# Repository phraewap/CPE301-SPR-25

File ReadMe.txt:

Name: Phraewa Pookprajob

UNLV Email: pookpraj@unlv.nevada.edu

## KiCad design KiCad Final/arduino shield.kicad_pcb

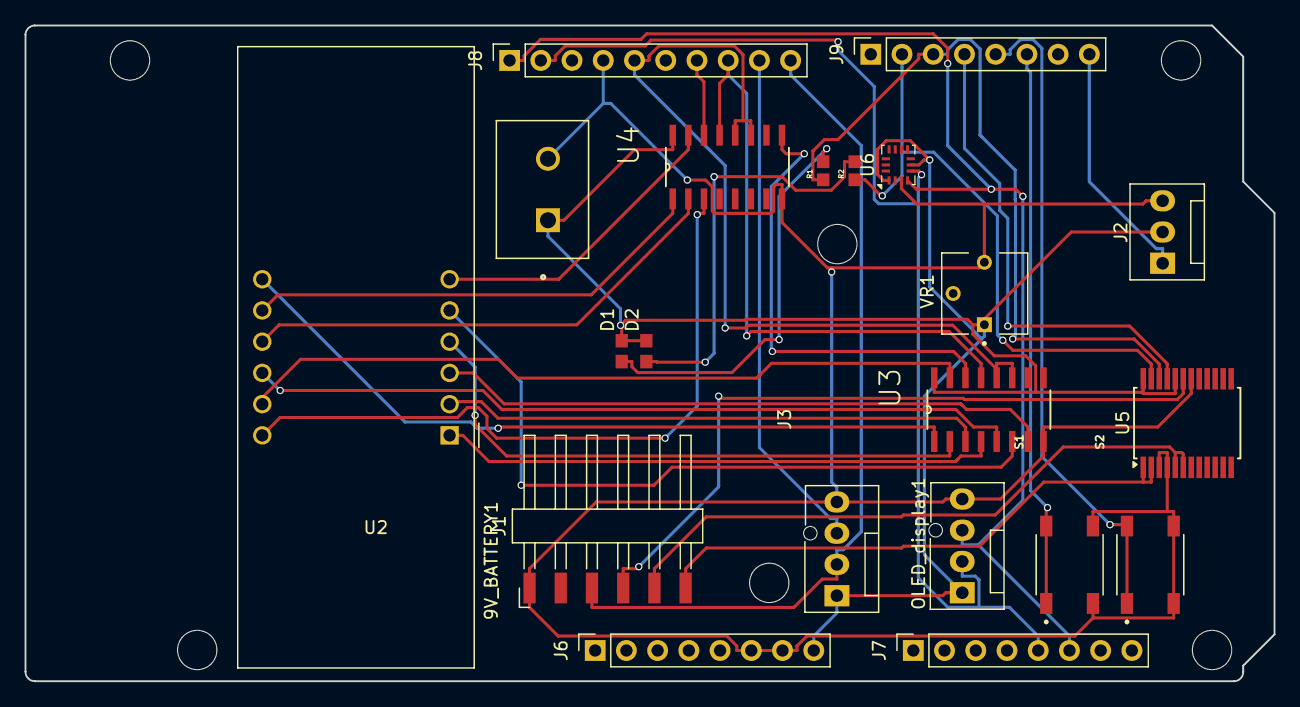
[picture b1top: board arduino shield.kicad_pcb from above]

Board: 2 copper layers, 101.6 x 53.3 mm, 27 parts (0 on the bottom side), 33 nets.

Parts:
9V_BATTERY1: OSTTC020162; OST_OSTTC020162
D1, D2: LTST-C193TGKT-5A; 0603
J1: Conn_01x06_Pin; Harwin_M20-89006xx_1x06_P2.54mm_Horizontal
J2: Conn_01x03_Pin; FanPinHeader_1x03_P2.54mm_Vertical
J3: Conn_01x04_Pin; FanPinHeader_1x04_P2.54mm_Vertical
J6: Power; PinSocket_1x08_P2.54mm_Vertical
J7: Analog; PinSocket_1x08_P2.54mm_Vertical
J8: PWM; PinSocket_1x10_P2.54mm_Vertical
J9: PWM; PinSocket_1x08_P2.54mm_Vertical
MH1, MH2, MH3, MH4, MH5, MH6: MountingHole_3.2mm
OLED_display1: Conn_01x04_Socket; FanPinHeader_1x04_P2.54mm_Vertical
R1, R2: RC0603JR-071KL; RESC1607X60N
S1, S2: 8-1437565-1; SW_8-1437565-1
U2: CC56-12SRWA; CA56-12SRWA
U3, U4: 74HC595D_118; SOIC127P600X175-16N
U5: TB6612FNG; SSOP-24_5.3x8.2mm_P0.65mm
U6: MY_BMI160; Bosch_LGA-14_3x2.5mm_P0.5mm
VR1: 3362P-1-103LF; TRIM_3362P-1-103LF

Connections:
GND: 9V_BATTERY1.2, J1.1, J2.3, J3.4, J6.6, J6.7, J8.4, OLED_display1.4, S1.3, S1.4, S2.3, S2.4, U3.8 (GND), U4.8 (GND), U5.3 (PGND1), U5.4 (PGND1), U5.18 (GND), U6.3 (GND), VR1.3
unnamed: D1.1, R1.2
unnamed: D2.1, R2.2
unnamed: J1.4, U5.19 (STBY)
unnamed: J1.5, U5.5 (AO2), U5.6 (AO2)
unnamed: J1.6, U5.1 (AO1), U5.2 (AO1)
unnamed: U2.12 (CC1), U4.3 (Q3)
unnamed: U2.9 (CC2), U4.2 (Q2)
unnamed: U2.8 (CC3), U4.1 (Q1)
unnamed: U2.6 (CC4), U4.15 (Q0)
unnamed: U2.3 (DPX), U3.7 (Q7)
unnamed: U2.11 (a), U3.15 (Q0)
unnamed: U2.7 (b), U3.1 (Q1)
unnamed: U2.4 (c), U3.2 (Q2)
unnamed: U2.2 (d), U3.3 (Q3)
unnamed: U2.1 (e), U3.4 (Q4)
unnamed: U2.10 (f), U3.5 (Q5)
unnamed: U2.5 (g), U3.6 (Q6)
unnamed: U3.14 (DS), U4.9 (Q7_2)
PB0/TRIG/DCMOTOR: J1.3, J3.2, J8.10
PB1/ECHO: J3.3, J8.9
PB2/SS: J8.8, U3.13 (~OE), U4.13 (~OE)
PB3/SPIDATA: J8.7, U4.14 (DS)
PB5/SPICLK: J8.5, U3.11 (SH_CP), U3.12 (ST_CP), U4.11 (SH_CP), U4.12 (ST_CP)
PC4/SCL0: J7.6, J8.1, OLED_display1.3, U6.4 (SCL)
PC5/SDA0: J7.5, J8.2, OLED_display1.2, U6.5 (SDA)
PD2: J9.6, S1.1, S1.2
PD3: J9.5, S2.1, S2.2
PD4: J9.4, U5.21 (AIN1)
PD5: J9.3, R1.1, U5.22 (AIN2)
PD6: J9.2, R2.1, U5.23 (PWMA)
SERVOPIN/PD0: J2.1, J9.8
VCC: 9V_BATTERY1.1, D1.2, D2.2, J2.2, J3.1, J6.8, OLED_display1.1, U3.16 (VCC), U4.16 (VCC), U5.20 (VCC), U5.24 (VM1), U6.1 (Vin), U6.6 (CS), VR1.1

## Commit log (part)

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2025-02-24 Add files via upload
    This is the folder created via Microchip Studio
2025-05-11 ReadMe.txt
2025-05-11 Create THIS IS DA6
